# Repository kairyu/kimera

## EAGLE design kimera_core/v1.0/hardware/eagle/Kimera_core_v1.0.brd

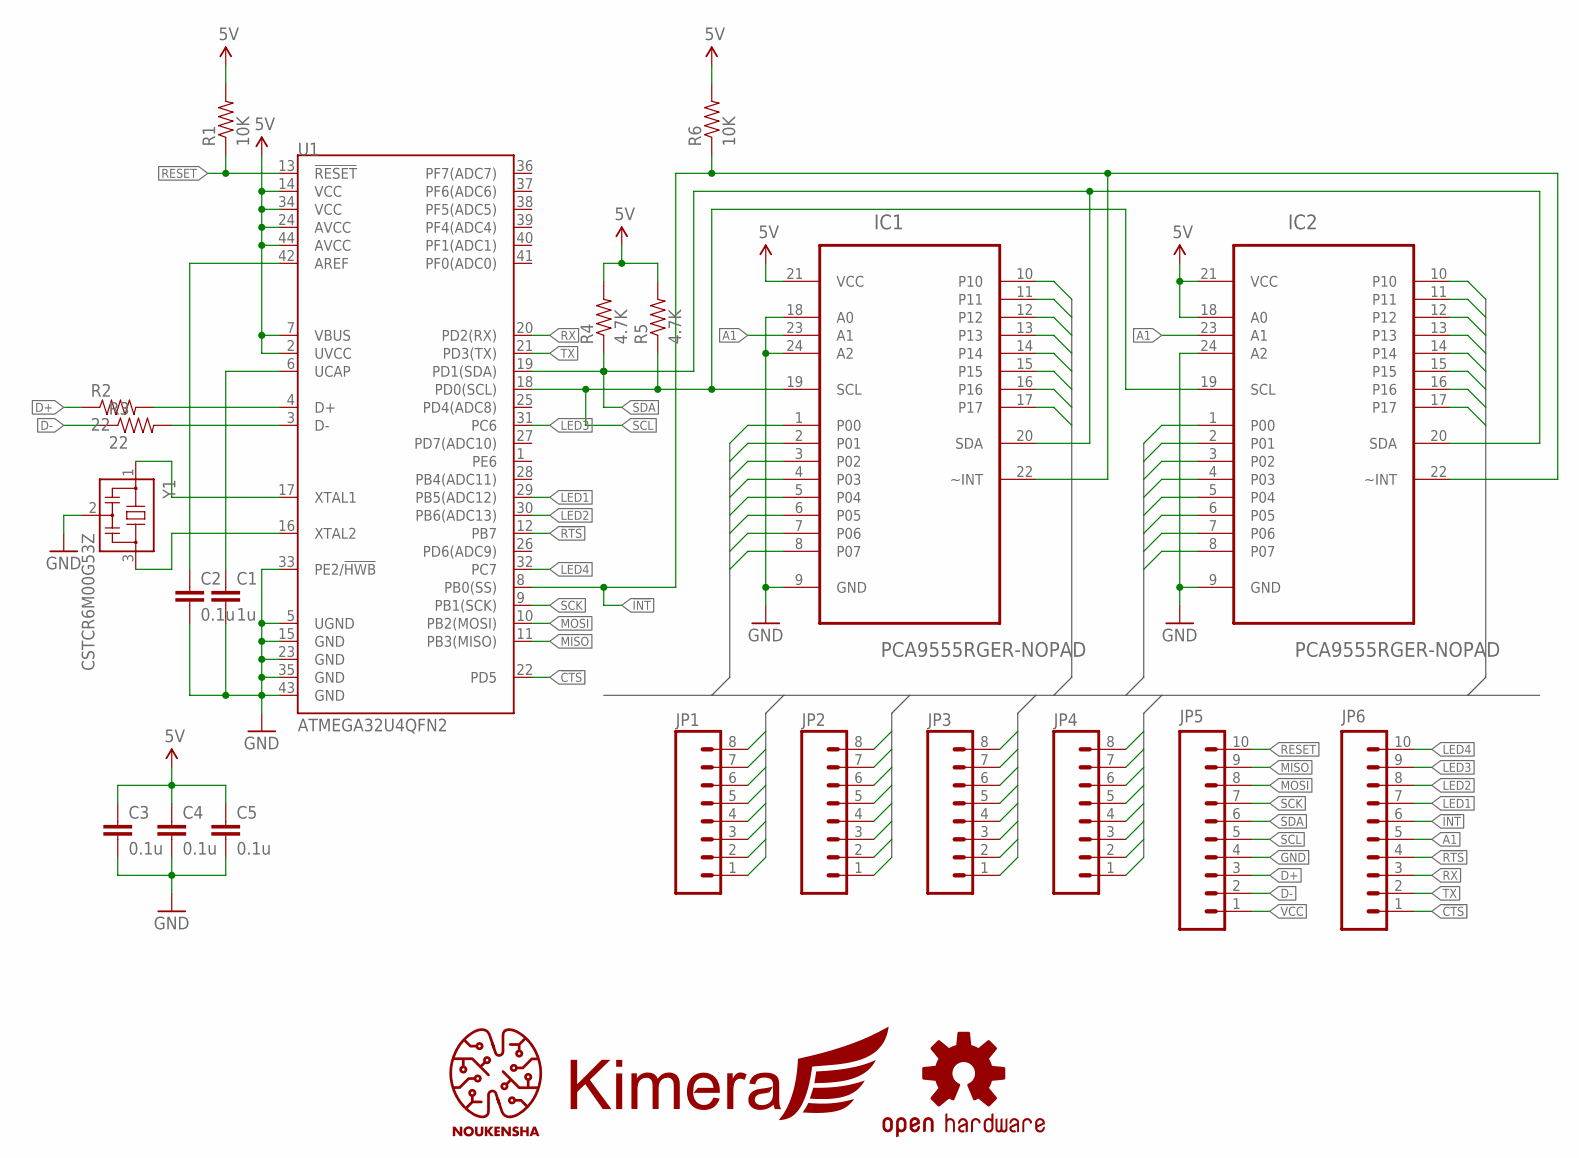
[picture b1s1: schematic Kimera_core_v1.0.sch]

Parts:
C1: 1u; 0402-CAP
C2, C3, C4, C5: 0.1u; 0402-CAP
IC1, IC2: PCA9555RGER-NOPAD; QFN50P400X400X100-25N-NOPAD
JP1, JP2, JP3, JP4: P08
JP5, JP6: P10
LOGO1: KIMERA_LOGO
LOGO2: NOUKENSHA_LOGONIX; NOUKENSHA_LOGO_NIX
LOGO3: OSHW_LOGONIX; OSHW_LOGO_NIX
R1, R6: 10K; 0402-RES
R2, R3: 22; 0402-RES
R4, R5: 4.7K; 0402-RES
U1: ATMEGA32U4QFN2; QFN-44-NOPAD
Y1: CSTCR6M00G53Z; CSTER12M

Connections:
!CTS: JP6.1, U1.22 (PD5)
!INT: IC1.22 (~INT), IC2.22 (~INT), JP6.6, R6.1, U1.8 (PB0(SS))
!RTS: JP6.4, U1.12 (PB7)
A1: IC1.23 (A1), IC2.23 (A1), JP6.5
D+: JP5.3, R2.1
D-: JP5.2, R3.1
GND: C1.2, C2.2, C3.2, C4.2, C5.2, IC1.9 (GND), IC1.18 (A0), IC1.24 (A2), IC2.9 (GND), IC2.24 (A2), JP5.4, U1.5 (UGND), U1.15 (GND), U1.23 (GND), U1.33 (PE2/!HWB), U1.35 (GND), U1.43 (GND), Y1.2
LED1: JP6.7, U1.29 (PB5(ADC12))
LED2: JP6.8, U1.30 (PB6(ADC13))
LED3: JP6.9, U1.31 (PC6)
LED4: JP6.10, U1.32 (PC7)
MISO: JP5.9, U1.11 (PB3(MISO))
MOSI: JP5.8, U1.10 (PB2(MOSI))
unnamed: C2.1, U1.42 (AREF)
unnamed: R2.2, U1.4 (D+)
unnamed: U1.17 (XTAL1), Y1.1
unnamed: U1.16 (XTAL2), Y1.3
unnamed: R3.2, U1.3 (D-)
unnamed: C1.1, U1.6 (UCAP)
P1: IC1.1 (P00), JP1.1
P2: IC1.2 (P01), JP1.2
P3: IC1.3 (P02), JP1.3
P4: IC1.4 (P03), JP1.4
P5: IC1.5 (P04), JP1.5
P6: IC1.6 (P05), JP1.6
P7: IC1.7 (P06), JP1.7
P8: IC1.8 (P07), JP1.8
P9: IC1.10, JP2.1
P10: IC1.11, JP2.2
P11: IC1.12, JP2.3
P12: IC1.13, JP2.4
P13: IC1.14, JP2.5
P14: IC1.15, JP2.6
P15: IC1.16, JP2.7
P16: IC1.17, JP2.8
P17: IC2.1 (P00), JP3.1
P18: IC2.2 (P01), JP3.2
P19: IC2.3 (P02), JP3.3
P20: IC2.4 (P03), JP3.4
P21: IC2.5 (P04), JP3.5
P22: IC2.6 (P05), JP3.6
P23: IC2.7 (P06), JP3.7
P24: IC2.8 (P07), JP3.8
P25: IC2.10, JP4.1
P26: IC2.11, JP4.2
P27: IC2.12, JP4.3
P28: IC2.13, JP4.4
P29: IC2.14, JP4.5
P30: IC2.15, JP4.6
P31: IC2.16, JP4.7
P32: IC2.17, JP4.8
RESET: JP5.10, R1.1, U1.13 (!RESET)
RX: JP6.3, U1.20 (PD2(RX))
SCK: JP5.7, U1.9 (PB1(SCK))
SCL: IC1.19 (SCL), IC2.19 (SCL), JP5.5, R5.1, U1.18 (PD0(SCL))
SDA: IC1.20 (SDA), IC2.20 (SDA), JP5.6, R4.1, U1.19 (PD1(SDA))
TX: JP6.2, U1.21 (PD3(TX))
VCC: C3.1, C4.1, C5.1, IC1.21 (VCC), IC2.18 (A0), IC2.21 (VCC), JP5.1, R1.2, R4.2, R5.2, R6.2, U1.2 (UVCC), U1.7 (VBUS), U1.14 (VCC), U1.24 (AVCC), U1.34 (VCC), U1.44 (AVCC)

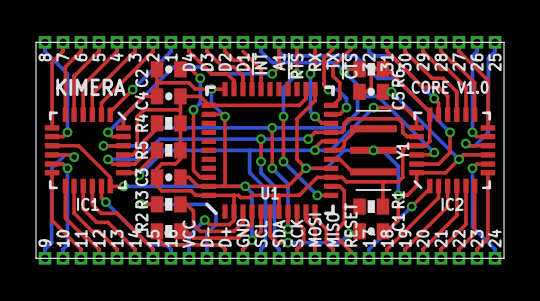
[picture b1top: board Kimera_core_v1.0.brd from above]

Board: 2 copper layers, 26.0 x 12.0 mm, 24 parts (1 on the bottom side), 58 nets.

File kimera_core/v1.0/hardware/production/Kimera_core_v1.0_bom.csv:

"Part","Value","Device","Package","Description","MF","MPN","OC_FARNELL","OC_NEWARK",
"C1","1u","CAP0402-CAP","0402-CAP","Capacitor","","","","",
"C2","0.1u","CAP0402-CAP","0402-CAP","Capacitor","","","","",
"C3","0.1u","CAP0402-CAP","0402-CAP","Capacitor","","","","",
"C4","0.1u","CAP0402-CAP","0402-CAP","Capacitor","","","","",
"C5","0.1u","CAP0402-CAP","0402-CAP","Capacitor","","","","",
"IC1","PCA9555RGER-NOPAD","PCA9555RGER-NOPAD","QFN50P400X400X100-25N-NOPAD","16-BIT I/O EXPANDER","","","","",
"IC2","PCA9555RGER-NOPAD","PCA9555RGER-NOPAD","QFN50P400X400X100-25N-NOPAD","16-BIT I/O EXPANDER","","","","",
"JP1","","P08","P08","","","","","",
"JP2","","P08","P08","","","","","",
"JP3","","P08","P08","","","","","",
"JP4","","P08","P08","","","","","",
"JP5","","P10","P10","","","","","",
"JP6","","P10","P10","","","","","",
"LOGO1","KIMERA_LOGO","KIMERA_LOGO","KIMERA_LOGO","","","","","",
"LOGO2","NOUKENSHA_LOGONIX","NOUKENSHA_LOGONIX","NOUKENSHA_LOGO_NIX","","","","","",
"LOGO3","OSHW_LOGONIX","OSHW_LOGONIX","OSHW_LOGO_NIX","Open Source Hardware Logo","","","","",
"R1","10K","RESISTOR0402-RES","0402-RES","Resistor","","","","",
"R2","22","RESISTOR0402-RES","0402-RES","Resistor","","","","",
"R3","22","RESISTOR0402-RES","0402-RES","Resistor","","","","",
"R4","4.7K","RESISTOR0402-RES","0402-RES","Resistor","","","","",
"R5","4.7K","RESISTOR0402-RES","0402-RES","Resistor","","","","",
"R6","10K","RESISTOR0402-RES","0402-RES","Resistor","","","","",
"U1","ATMEGA32U4QFN2","ATMEGA32U4QFN2","QFN-44-NOPAD","Atmel 44-pin 8-bit Microcontroller with 32KBytes of ISP Flash and USB Controller","","","","",
"Y1","CSTCR6M00G53Z","CSTCR6M00G53Z","CSTER12M","Resonator","","CSTCC12M0","1170434","25M8759",

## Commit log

2014-06-09 Add some docs
2014-06-09 Add schematic file of kimera v1
2014-06-17 Add a image version of schematic
2016-06-07 Move old documents to kimera_origin
2016-06-07 Add license CC BY-SA 4.0
2016-06-07 kimera_core: Initial schematic and layout of v1.0
2016-06-07 kimera_core: Change bus and layout
2016-06-07 kimera_core: Change basic layout and route a part of io
2016-06-07 kimera_core: Assign main io and route more io
2016-06-07 kimera_core: Change element location and castellated holes
2016-06-07 kimera_core: Reduce board size and remove some main io
2016-06-07 kimera_core: First complete version - Finish routing - Add logo and silk screen
2016-06-07 kimera_core: Add production files
2016-06-07 kimera_core: Change signal name of LED pins
2016-06-07 kimera_core: Add schematic files

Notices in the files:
parts and their libraries:
SparkFun-DigitalIC: Licensing: Creative Commons ShareAlike 4.0 International - https://creativecommons.org/licenses/by-sa/4.0
